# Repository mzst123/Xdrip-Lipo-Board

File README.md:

# Xdrip Lipo Bluetooth Board PCB
Xdrip on a printed circuit board!

The design files are in the folder ["Eagle PCB Files"](https://github.com/mzst123/Xdrip-Lipo-Board/tree/master/Eagle%20PCB%20Files)

Or you can order the PCB directly [here](https://oshpark.com/shared_projects/IuYnoGB9)

For other versions of this project check out the folder ["Other Versions"](https://github.com/mzst123/Xdrip-Lipo-Board/tree/master/Other%20Versions)

If you can't solder this board and need help send me an email and im sure we can figure something out. My e-mail address is my github username at gmail.com

## Features:

- The board uses a MAX1811 battery charging ic
- Both Xbridge & Xdrip circuit support, selectable via a switch
- Battery can be soldered directly on the PCB (2.54mm header) or via a JST-2 connector (2mm pitch)
- Charging Status LED (On = charging; off = full)

## Components:

- 3x 1206 SMD Resitors (150Ω, 10kΩ, 27kΩ)
- 2x 1206 SMD Capacitor 10μf
- 2x micro switch MSK-12C02
- 1x 1206 Red LED (any led should work)
- 1x micro usb socket (ebay id: 121829362799)
- 1x MAX1811 lithium charger IC
- 1x [JST-2 connector 2mm pitch](https://www.sparkfun.com/products/8612) (optional - your battery needs to have the mating connector - sparkfun sells compatible batteries, or buy the connector separately and crimp it on your battery)
- 1x HM-11 Bluetooth V4.0 Transceiver BLE Module (I got the one from fasttech)
- 1x Polulu Wixel
- 1x LiPo/Li-ion Battery (I recommend using a LiPo battery)

Attention! The MAX1811 Charger IC is set to 500mah. Only use a battery with more than 500mah.

I source most of my components from eBay because of the free shipping. Here are some example links but consider that the prices change daily and shipping depends on where you are located:
- [Resistors](http://www.ebay.com/itm/100pcs-1-4W-watt-1206-SMT-SMD-Chip-Resistor-from-0-ohm-to-10M-ohm-1-/252380762812?var=&hash=item3ac310d2bc:m:msXv_-i2Opl1RPDANdY3cMw)
- [Capacitors](http://www.ebay.com/itm/12pcs-1206-smd-tantalum-capacitor-16v-10uf-106-10-3216-a-type-ic-diy-develop-d1-/331840663464?hash=item4d433eafa8:g:MpYAAOSwubRXFXfc)
- [Micro Switch](http://www.ebay.com/itm/20-pcs-MSK-12C02-Mini-SPDT-1P2T-Slide-Switch-On-Off-SMD-7-Pin-For-MP3-MP4-/161857451517?hash=item25af74b5fd:g:e1IAAOSwl9BWHbT4)
- [Red Led](http://www.ebay.com/itm/10-x-1206-RED-Super-Bright-LED-Chip-SMD-SMT-Bulb-Lamp-Light-High-Brightness-RoHs-/191231419928?hash=item2c8647e618:g:O3sAAOSw9N1Vo3OF&vxp=mtr)
- [micro usb socket](http://www.ebay.com/itm/2015-New-10Pcs-Micro-USB-B-Female-5Pin-SMT-Socket-Connector-Hot-Sale-MO-/401091696043?hash=item5d62ed95ab:g:R2kAAOSwDNdVpfv5)
- [Max1811](http://www.ebay.com/itm/1PCS-USB-LI-CHARGER-IC-MAXIM-SOP-8-MAX1811ESA-MAX1811ESA-MAX1811ESA-T-/272041007390?hash=item3f56e8591e:g:rx0AAOSwAYtWPgb~)
- [LiPo battery](http://www.ebay.com/itm/3-7V-850mAh-Lipo-Polymer-li-ion-Battery-703040-for-cell-phone-Camera-DVD-GPS-PAD-/111909510772?hash=item1a0e539e74:g:FAoAAOSwFNZWxojb)
- [Bluetooth module(Fasttech)](https://www.fasttech.com/product/1740900-hm-11-bluetooth-v4-0-transceiver-ble-module)

## PCB Assembly:

Everything is labeled on the PCB. The components are large enough to be soldered by hand, the trickiest for me was the micro usb socket. But if you use a hot air rework station (40$ on ebay) it should be very easy.

Here is a video how-to:

## Schematics:

## Software:
For the Wixel software i recommend [xBridge](https://github.com/jstevensog/wixel-sdk/tree/master/apps/xBridge2) from [John] (https://github.com/jstevensog). Just download the .wxl file and load it to the wixel. There are many advantages of xBridge, for example you don't have to re-compile the program to change transmitters because you can set it inside the xDrip app, improoved power saving features, battery level estimate, etc...

[Here](https://github.com/StephenBlackWasAlreadyTaken/xDrip/wiki/xdrip-beta) you can download the latest xDrip android app.

## 3D Enclosure:

I made an enclosure, however it still has to be improved. To further reduce space, the JST-2 connector is not used in this design. In the future I might add one with JST-2 support. The battery compartment should fit an 850mah Lipo Battery (7x30x40mm). For more information and to download the .STL files go to the ["Enclosure"](https://github.com/mzst123/Xdrip-Lipo-Board/tree/master/Enclosure) Folder.

## Pictures:

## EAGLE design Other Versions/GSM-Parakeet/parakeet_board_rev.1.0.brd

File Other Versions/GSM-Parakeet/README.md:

# GSM / Parakeet Version

# Tested & Works!
To order the PCB click [here](https://oshpark.com/shared_projects/pyIarV64).

This version uses a GSM module (SIM800L) instead of bluetooth. Check the [Parakeet project](https://jamorham.github.io/) for more info.

I had to switch to the TP4056 Charging IC because it has more power and is cheaper.

## Features:

- The board uses a TP4056 battery charging ic with a maximum charging power of 1000mA
- SIM800L Module sends the CGM data directly to the cloud
- Charging Status LED, Red = charging; Green = Full
- 4 ways to connect the battery: 
- - [JST-2 (sparkfun batteries, 2mm pitch)](https://www.sparkfun.com/products/341)
- - [JST-XH (ebay batteries, 2.54mm pitch)](http://www.ebay.com/itm/231387564843?_trksid=p2057872.m2749.l2648&ssPageName=STRK%3AMEBIDX%3AIT)
- - [2.54mm pitch screw-in connector](http://www.ebay.com/itm/2pcs-2-Poles-2-Pin-2-54mm-0-1-PCB-Universal-Screw-Terminal-Block-Connector-/262007114779?hash=item3d00d74c1b:g:5OIAAOSwPcVVwJQX)
- - Solder the wires directly

## Changelog
rev.1.0 - added JST-XH footprint, improoved pcb traces and vias

rev.0.9 - fixed SIM800L footprint, improoved pcb traces and vias

rev.0.8 - first version ready to manufacture

# Components

Most can be sourced from eBay

- SIM800L GSM Module
- 1x Polulu Wixel
- TP4056 Li Charging IC
- 2x 10μf Capacitors
- 1x 1.2kΩ Resistor (RPROG - 1.2kΩ=1000mA - Depends on Charging current - Check table below)
- 2x 330Ω Resistor
- 2x 1206 LED (1 Red and 1 Green)
- 1x [Micro USB Connector Female 4Legs](http://www.ebay.com/itm/10Pcs-Micro-USB-Type-B-Female-Socket-4-Vertical-Legs-For-Solder-Connectors-/351570406777?hash=item51db3aad79:g:UUwAAOSwu-BWOscw)
- 1x micro switch MSK-12C02
- 1x LiPo/Li-ion Battery (I recommend using a LiPo battery)
- 1x [JST-2 connector 2mm pitch](https://www.sparkfun.com/products/8612) (optional - your battery needs to have the mating connector - sparkfun sells compatible batteries, or buy the connector separately and crimp it on your battery)
- 1x JST-XH 2-pin connector (optional - only if your battery has this type of connector or you plan on crimping your own)

# Setting the charging current

You can individually set the charging current. Just change the RPROG resistor to the value you want.
The charging Current should be set dependent on the battery used. Always use a charging current equal or lower than the battery capacity.

|RPROG (kΩ)|IBAT(mA)| 
|:--------:|:------:|
|10        |130     |
|5         |250     |
|4         |300     |
|3         |400     |
|2         |580     |
|1.66      |690     |
|1.5       |780     |
|1.33      |900     |
|1.2       |1000    |

## Schematics:

## Pictures:

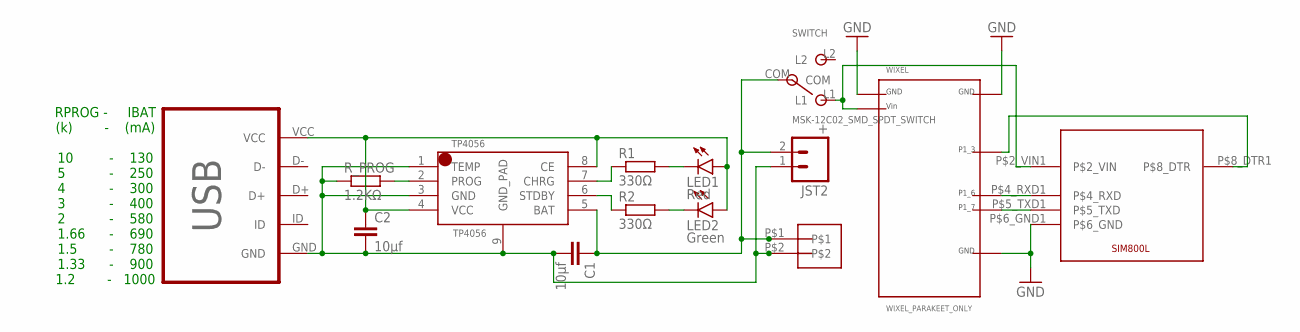
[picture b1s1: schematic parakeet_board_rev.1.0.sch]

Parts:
C1, C2: 10μf; C1206
JST2: +; JST-2-SMD
JST-XH: 2_PIN_JST-XH-B2B
LED1: Red; LED-1206
LED2: Green; LED-1206
R1, R2: 330Ω; R1206
R_PROG: 1.2KΩ; R1206
SIM800L: SIM800L_PARAKEET_ONLY
SWITCH: MSK-12C02_SMD_SPDT_SWITCH; MSK-12C02
TP4056: TP4056; SOP-8
USB: MICRO-USB-B; MICRO_USB_4_LEGS
WIXEL: WIXEL_PARAKEET_ONLY

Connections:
GND: C1.2, C2.2, JST2.1 (2), JST-XH.P$2, R_PROG.1, SIM800L.P$6_GND1 (P$6_GND), TP4056.1 (TEMP), TP4056.3 (GND), TP4056.9 (GND_PAD), USB.GND, WIXEL.P$1 (P$1-GND1), WIXEL.P$12 (P$12-GND2), WIXEL.P$23 (P$23-GND3)
unnamed: R_PROG.2, TP4056.2 (PROG)
unnamed: SIM800L.P$5_TXD1 (P$5_TXD), WIXEL.P$20 (P$20-P1_7)
unnamed: LED1.C, R1.2
unnamed: LED2.C, R2.2
unnamed: R1.1, TP4056.7 (CHRG)
unnamed: R2.1, TP4056.6 (STDBY)
unnamed: C2.1, LED1.A, LED2.A, TP4056.4 (VCC), TP4056.8 (CE), USB.VCC
unnamed: C1.1, JST2.2 (1), JST-XH.P$1, SWITCH.COM, TP4056.5 (BAT)
unnamed: SIM800L.P$4_RXD1 (P$4_RXD), WIXEL.P$19 (P$19-P1_6)
unnamed: SIM800L.P$2_VIN1 (P$2_VIN), SWITCH.L1, WIXEL.P$2 (P$2-VIN)
unnamed: SIM800L.P$8_DTR1 (P$8_DTR), WIXEL.P$16 (P$16-P1_3)

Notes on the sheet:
RPROG - IBAT (k) - (mA) 10 - 130 5 - 250 4 - 300 3 - 400 2 - 580 1.66 - 690 1.5 - 780 1.33 - 900 1.2 - 1000

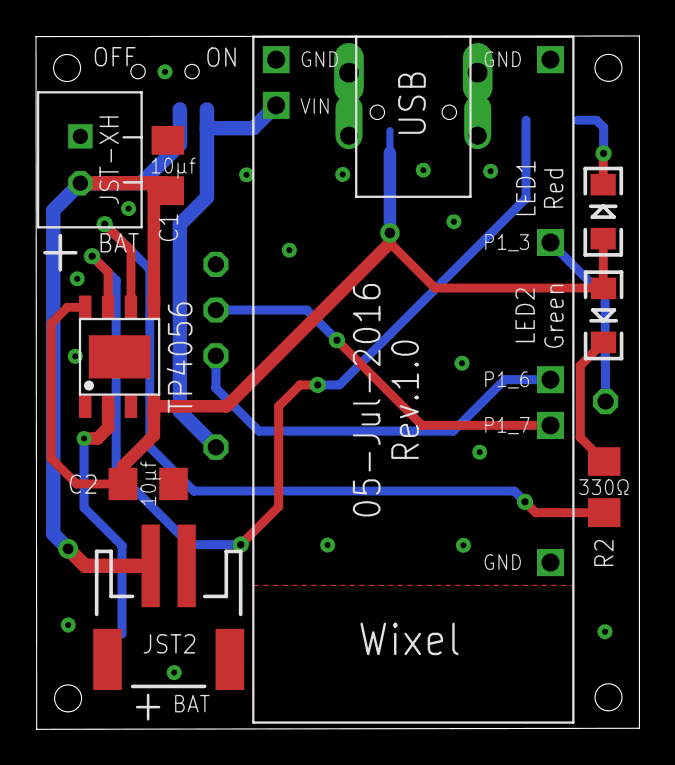
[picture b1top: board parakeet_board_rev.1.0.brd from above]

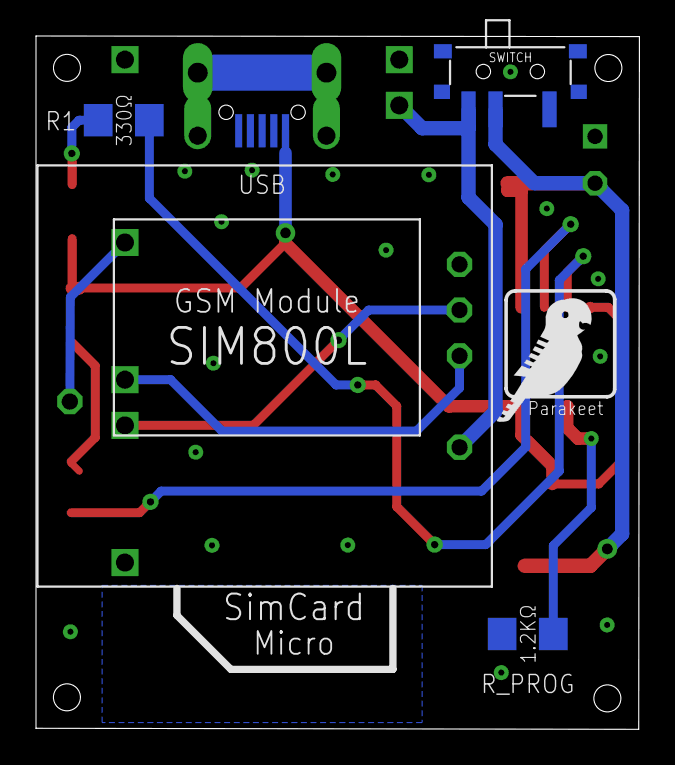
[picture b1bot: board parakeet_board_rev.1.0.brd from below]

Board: 2 copper layers, 33.5 x 38.5 mm, 15 parts (6 on the bottom side), 12 nets.

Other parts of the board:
U$2: PARAKEET

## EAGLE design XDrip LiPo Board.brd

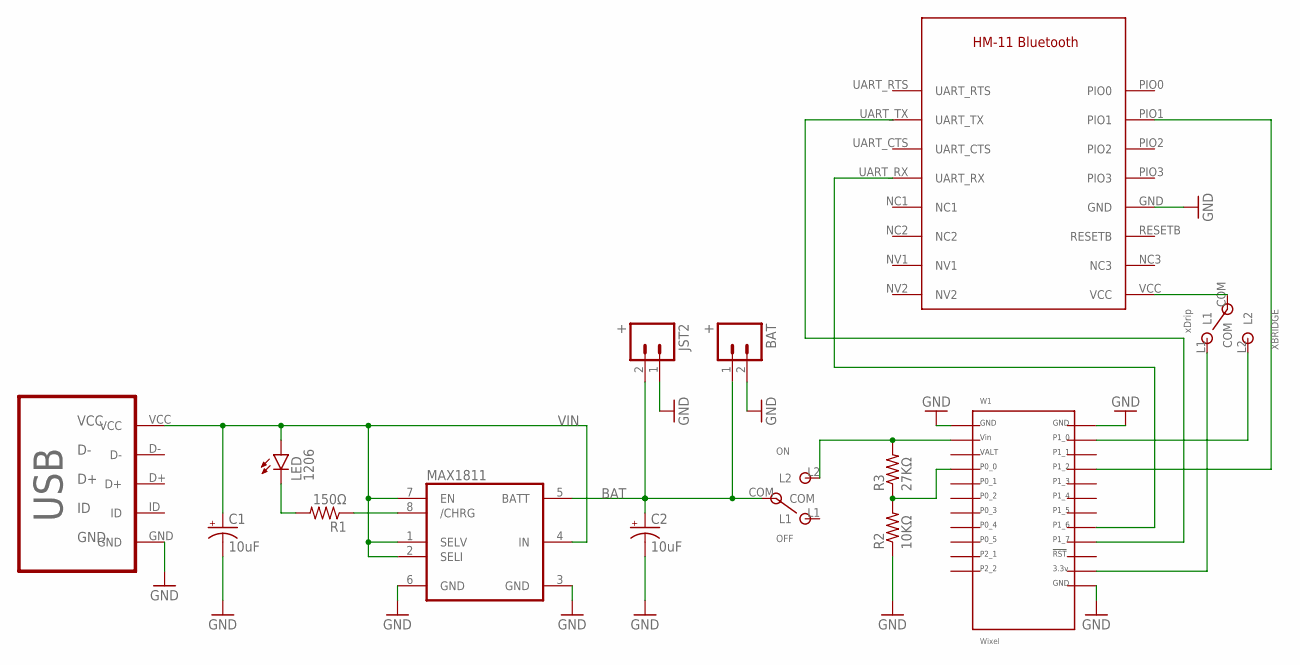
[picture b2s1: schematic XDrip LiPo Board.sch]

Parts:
BAT: +; 1X02
C1, C2: 10uF; EIA3216
JST2: +; JST-2-SMD
LED: 1206; LED-1206
MAX1811: MAX1811; SO08
ON: OFF; MSK-12C02
R1: 150Ω; 1206
R2: 10KΩ; 1206
R3: 27KΩ; 1206
U$2: HM-11
U$3: MICRO-USB-B; USB-AB-MICRO-SMD_V02_BOSS
W1: Wixel; WIXEL
XBRIDGE: xDrip; MSK-12C02

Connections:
BAT: BAT.1, C2.A (+), JST2.2 (1), MAX1811.5 (BATT), ON.COM
GND: BAT.2, C1.C (-), C2.C (-), JST2.1 (2), MAX1811.3 (GND), MAX1811.6 (GND), R2.1, U$2.GND, U$3.GND, W1.P$1, W1.P$12, W1.P$23
unnamed: U$2.VCC, XBRIDGE.COM
unnamed: LED.C, R1.2
unnamed: MAX1811.8 (/CHRG), R1.1
unnamed: ON.L2, R3.2, W1.P$2
unnamed: R2.2, R3.1, W1.P$4
unnamed: W1.P$13, XBRIDGE.L2
unnamed: U$2.PIO1, W1.P$15
unnamed: W1.P$22, XBRIDGE.L1
RX: U$2.UART_RX, W1.P$19
TX: U$2.UART_TX, W1.P$20
VIN: C1.A (+), LED.A, MAX1811.1 (SELV), MAX1811.2 (SELI), MAX1811.4 (IN), MAX1811.7 (EN), U$3.VCC

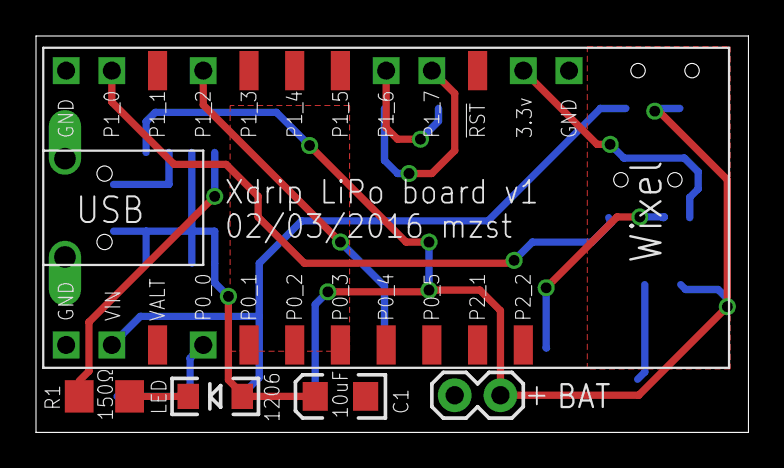
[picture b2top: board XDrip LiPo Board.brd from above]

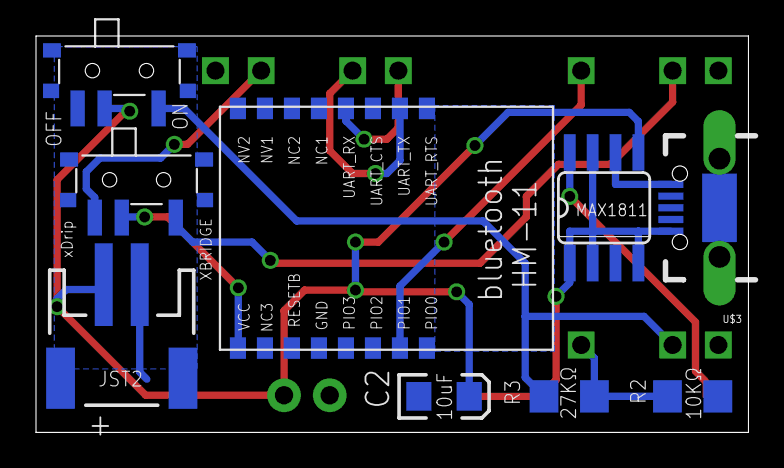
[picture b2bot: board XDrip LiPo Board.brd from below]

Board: 2 copper layers, 39.6 x 22.0 mm, 14 parts (9 on the bottom side), 13 nets.

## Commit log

2016-04-22 Summary
    Description
2016-04-26 Added 3D Enclosure
2016-04-26 Updated Images
2016-05-03 Updated Folder
2016-05-03 Updated image folder
2016-05-03 Uploaded Fusion design files
2016-06-08 Added Parakeet Version
2016-06-08 Updated image
2016-06-12 Updated GSM version
2016-06-20 updated enclosure
2016-07-03 Updated Parakeet rev.09
    Fixed SIM800 module dimensions
2016-07-05 updated parakeet version
2016-07-13 Added 3D enclosure pictures

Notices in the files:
parts and their libraries:
SparkFun-Connectors: Licensing: Creative Commons ShareAlike 4.0 International - https://creativecommons.org/licenses/by-sa/4.0
